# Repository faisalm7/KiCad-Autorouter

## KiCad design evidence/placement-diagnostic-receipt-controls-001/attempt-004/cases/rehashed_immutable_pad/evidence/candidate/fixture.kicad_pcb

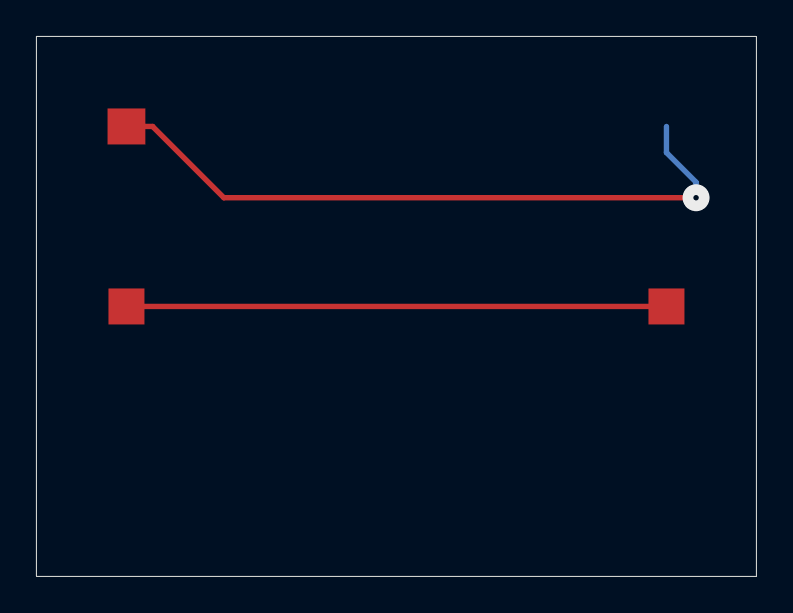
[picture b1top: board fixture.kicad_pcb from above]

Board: 2 copper layers, 40.0 x 30.0 mm, 4 parts (1 on the bottom side), 2 nets.

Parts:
J1, J2, J3, J4: floor_control_terminal

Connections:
SIGNAL_A: J1.1, J2.1
SIGNAL_B: J3.1, J4.1

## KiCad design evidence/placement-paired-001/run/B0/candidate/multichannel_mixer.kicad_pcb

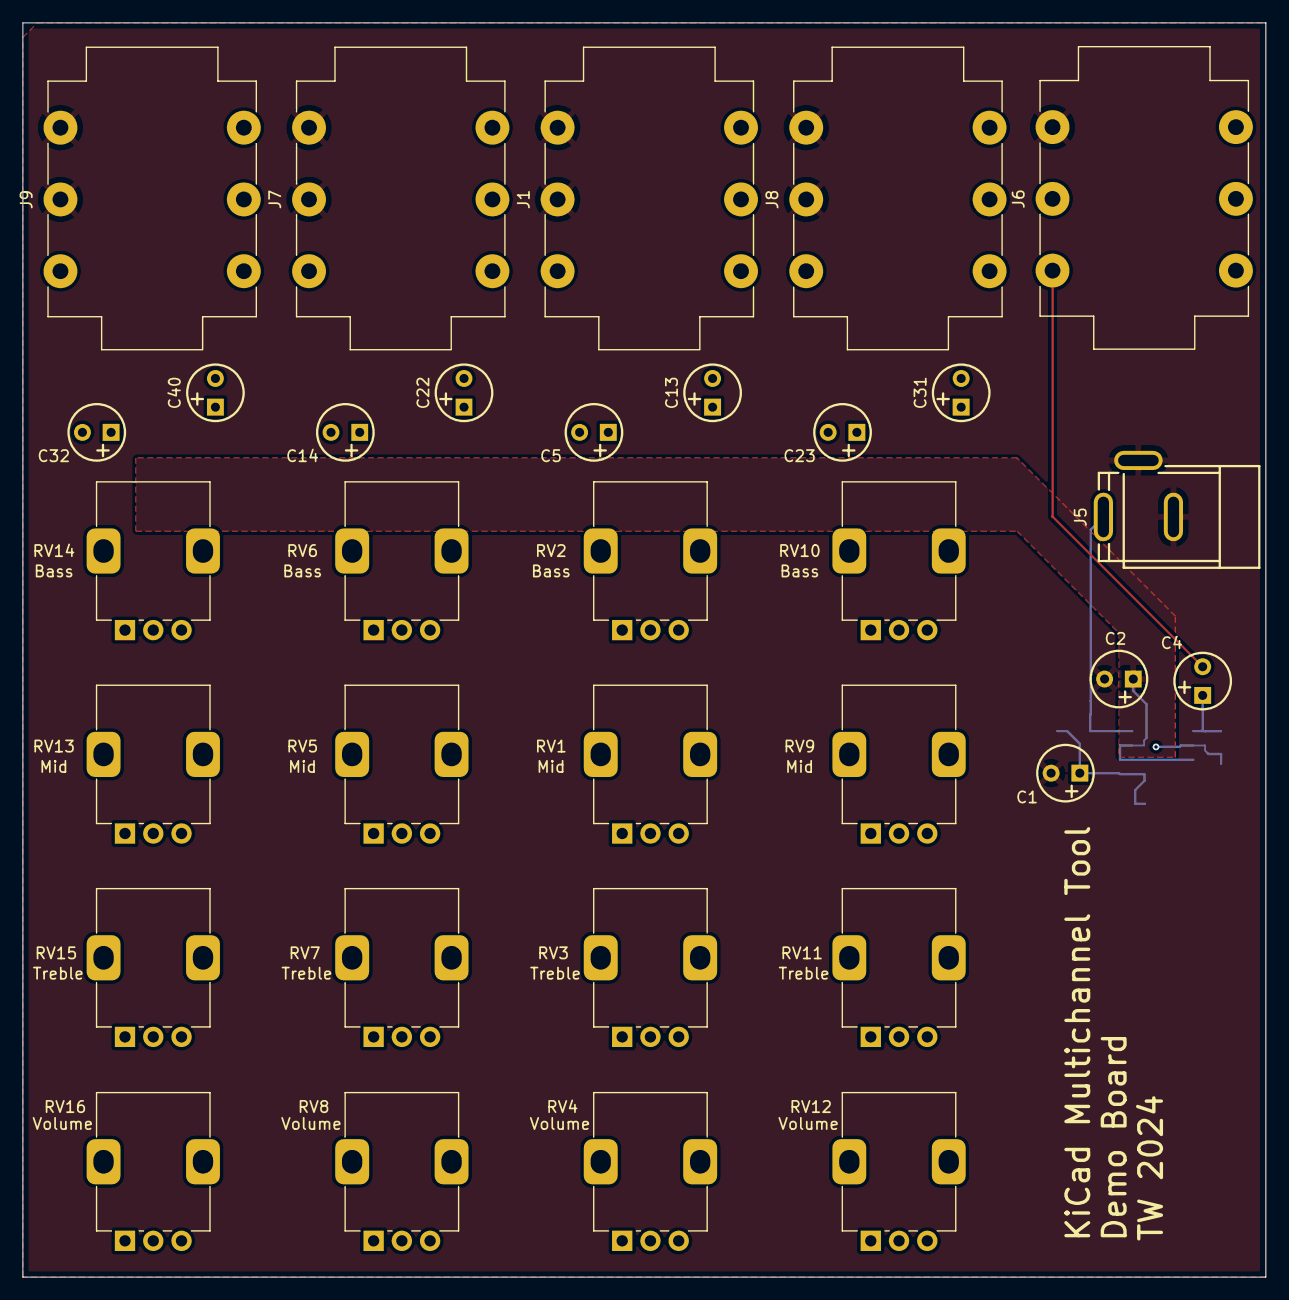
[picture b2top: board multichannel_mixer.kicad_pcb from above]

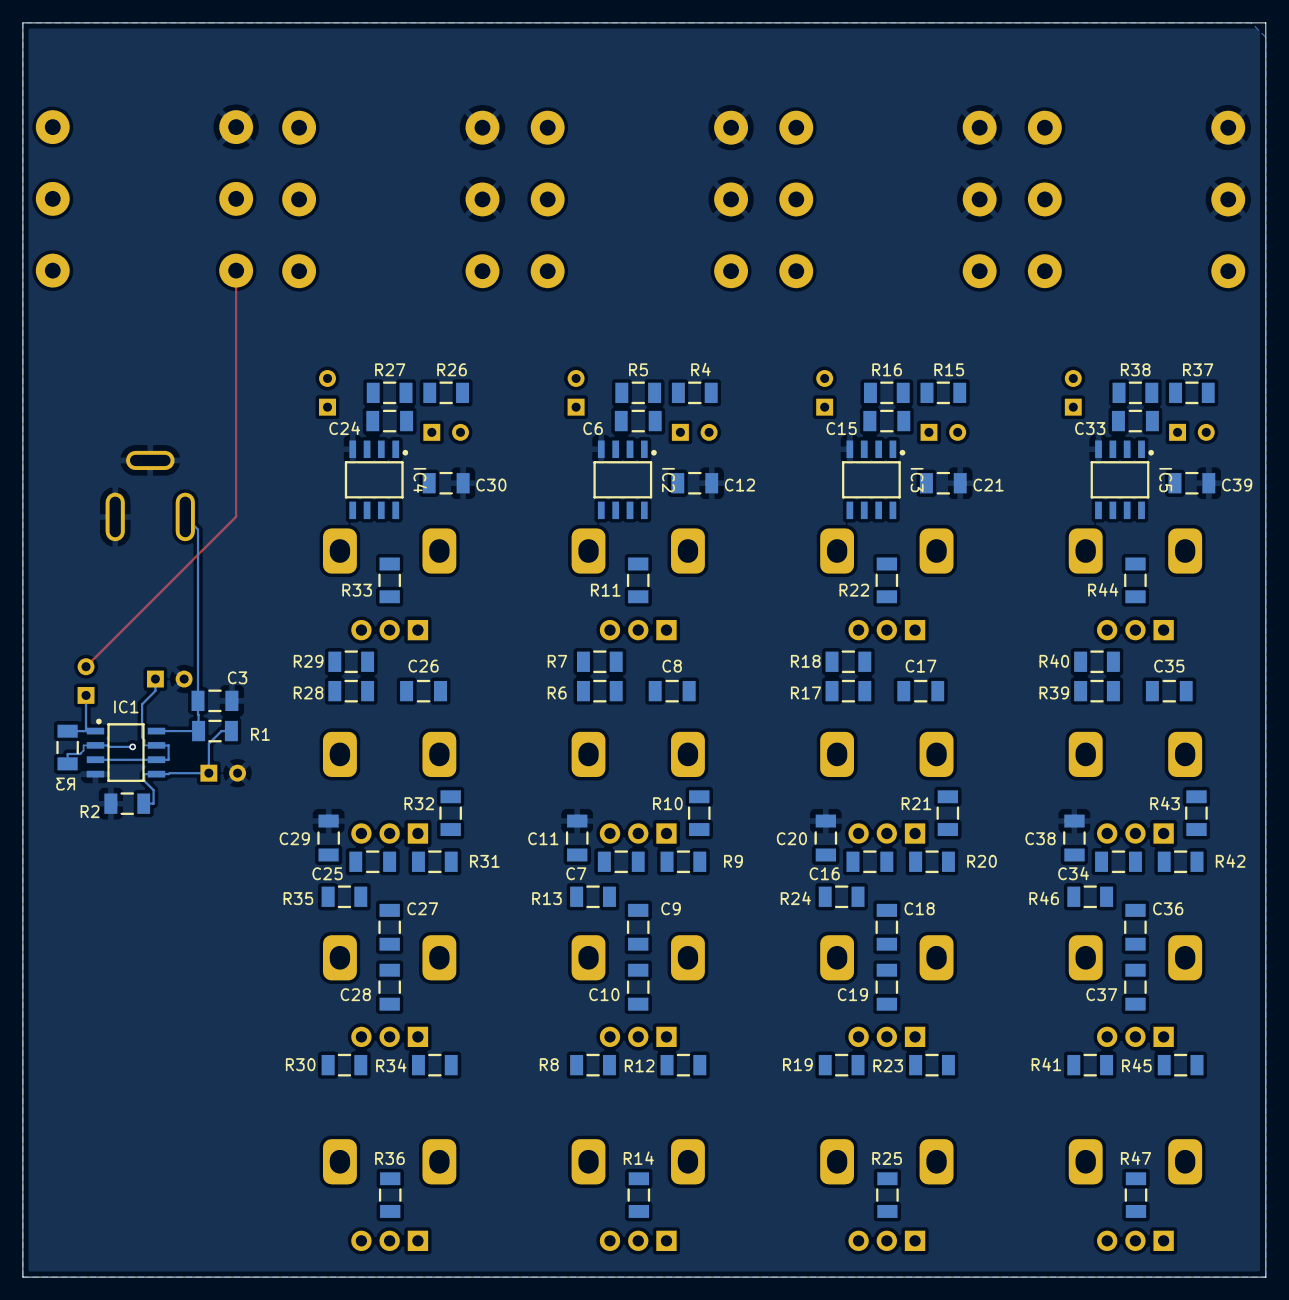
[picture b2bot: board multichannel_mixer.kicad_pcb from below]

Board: 2 copper layers, 110.0 x 111.0 mm, 114 parts (81 on the bottom side), 79 nets.

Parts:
C1, C2, C4, C5, C13, C14, C22, C23, C31, C32, C40: CTEB_2.2UF_35V_10%_254-500X840; CAPPRB254-500X840
C3, C6, C7, C8, C9, C10, C11, C12, C15, C16, C17, C18, C19, C20, C21, C24, C25, C26, C27, C28, C29, C30, C33, C34, C35, C36, C37, C38, C39: CC1206_100NF_50V_10%_X7R; CAPC3216X140N
IC1, IC2, IC3, IC4, IC5: TL072CD; SOIC127P600X175-8N
J1, J6, J7, J8, J9: CH1; Jack_6.35mm_Neutrik_NMJ6HCD2_Horizontal
J5: Power; CLIFF_FC68148(DC-10A)
R1, R2, R3, R4, R5, R6, R7, R8, R9, R10, R11, R12, R13, R14, R15, R16, R17, R18, R19, R20, R21, R22, R23, R24, R25, R26, R27, R28, R29, R30, R31, R32, R33, R34, R35, R36, R37, R38, R39, R40, R41, R42, R43, R44, R45, R46, R47: R1206_10K_1%_0.25W_100PPM; RESC3216X65N
RV1, RV5, RV9, RV13: Mid; Potentiometer_Alps_RK09K_Single_Vertical
RV2, RV6, RV10, RV14: Bass; Potentiometer_Alps_RK09K_Single_Vertical
RV3, RV7, RV11, RV15: Treble; Potentiometer_Alps_RK09K_Single_Vertical
RV4, RV8, RV12, RV16: Volume; Potentiometer_Alps_RK09K_Single_Vertical

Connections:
+12V: C3.2, C12.2, C21.2, C30.2, C39.2, IC1.8 (V+), IC2.8 (V+), IC3.8 (V+), IC4.8 (V+), IC5.8 (V+), J5.1, R1.2
/CH1/OUT: C13.2, C22.2, C31.2, C40.2, IC1.2 (IN-), R3.1
GND: C1.2, C2.2, C3.1, C11.1, C12.1, C20.1, C21.1, C29.1, C30.1, C38.1, C39.1, IC1.4 (V-), IC2.4 (V-), IC3.4 (V-), IC4.4 (V-), IC5.4 (V-), J1.R, J1.S, J5.2, J5.3, J6.S, J7.R, J7.S, J8.R, J8.S, J9.R, J9.S, R2.1
unnamed: C4.2, J6.T
unnamed: C5.1, R4.1
unnamed: C5.2, J1.T
unnamed: C7.1, R6.2, RV1.3
unnamed: C7.2, R9.1, RV1.1
unnamed: C8.1, R7.2, RV2.3
unnamed: C8.2, R10.1, RV2.1
unnamed: C9.1, RV1.2
unnamed: C10.1, RV3.2
unnamed: C11.2, R13.1
unnamed: C13.1, R14.2
unnamed: C14.1, R15.1
unnamed: C14.2, J7.T
unnamed: C16.1, R17.2, RV5.3
unnamed: C16.2, R20.1, RV5.1
unnamed: C17.1, R18.2, RV6.3
unnamed: C17.2, R21.1, RV6.1
unnamed: C18.1, RV5.2
unnamed: C19.1, RV7.2
unnamed: C20.2, R24.1
unnamed: C22.1, R25.2
unnamed: C23.1, R26.1
unnamed: C23.2, J8.T
unnamed: C25.1, R28.2, RV9.3
unnamed: C25.2, R31.1, RV9.1
unnamed: C26.1, R29.2, RV10.3
unnamed: C26.2, R32.1, RV10.1
unnamed: C27.1, RV9.2
unnamed: C28.1, RV11.2
unnamed: C29.2, R35.1
unnamed: C31.1, R36.2
unnamed: C32.1, R37.1
unnamed: C32.2, J9.T
unnamed: C34.1, R39.2, RV13.3
unnamed: C34.2, R42.1, RV13.1
unnamed: C35.1, R40.2, RV14.3
unnamed: C35.2, R43.1, RV14.1
unnamed: C36.1, RV13.2
unnamed: C37.1, RV15.2
unnamed: C38.2, R46.1
unnamed: C40.1, R47.2
unnamed: C4.1, IC1.1 (OUT), R3.2
unnamed: C1.1, IC1.5 (IN+), R1.1, R2.2
unnamed: C6.1, IC2.2 (IN-), R4.2, R5.1
unnamed: C6.2, IC2.1 (OUT), R5.2, R6.1, R7.1, R8.2
unnamed: C9.2, C10.2, IC2.6 (IN-), R11.2, R13.2
unnamed: IC2.7 (OUT), R9.2, R10.2, R12.1, RV4.3
unnamed: C15.1, IC3.2 (IN-), R15.2, R16.1
unnamed: C15.2, IC3.1 (OUT), R16.2, R17.1, R18.1, R19.2
unnamed: C18.2, C19.2, IC3.6 (IN-), R22.2, R24.2
unnamed: IC3.7 (OUT), R20.2, R21.2, R23.1, RV8.3
unnamed: C24.1, IC4.2 (IN-), R26.2, R27.1
unnamed: C24.2, IC4.1 (OUT), R27.2, R28.1, R29.1, R30.2
unnamed: C27.2, C28.2, IC4.6 (IN-), R33.2, R35.2
unnamed: IC4.7 (OUT), R31.2, R32.2, R34.1, RV12.3
unnamed: C33.1, IC5.2 (IN-), R37.2, R38.1
unnamed: C33.2, IC5.1 (OUT), R38.2, R39.1, R40.1, R41.2
unnamed: C36.2, C37.2, IC5.6 (IN-), R44.2, R46.2
unnamed: IC5.7 (OUT), R42.2, R43.2, R45.1, RV16.3
unnamed: R8.1, RV3.1
unnamed: R11.1, RV2.2
unnamed: R12.2, RV3.3
unnamed: R14.1, RV4.1, RV4.2
unnamed: R19.1, RV7.1
unnamed: R22.1, RV6.2
unnamed: R23.2, RV7.3
unnamed: R25.1, RV8.1, RV8.2
unnamed: R30.1, RV11.1
unnamed: R33.1, RV10.2
unnamed: R34.2, RV11.3
unnamed: R36.1, RV12.1, RV12.2
unnamed: R41.1, RV15.1
unnamed: R44.1, RV14.2
unnamed: R45.2, RV15.3
unnamed: R47.1, RV16.1, RV16.2
vbias: C2.1, IC1.3 (IN+), IC1.6 (IN-), IC1.7 (OUT), IC2.3 (IN+), IC2.5 (IN+), IC3.3 (IN+), IC3.5 (IN+), IC4.3 (IN+), IC4.5 (IN+), IC5.3 (IN+), IC5.5 (IN+)
